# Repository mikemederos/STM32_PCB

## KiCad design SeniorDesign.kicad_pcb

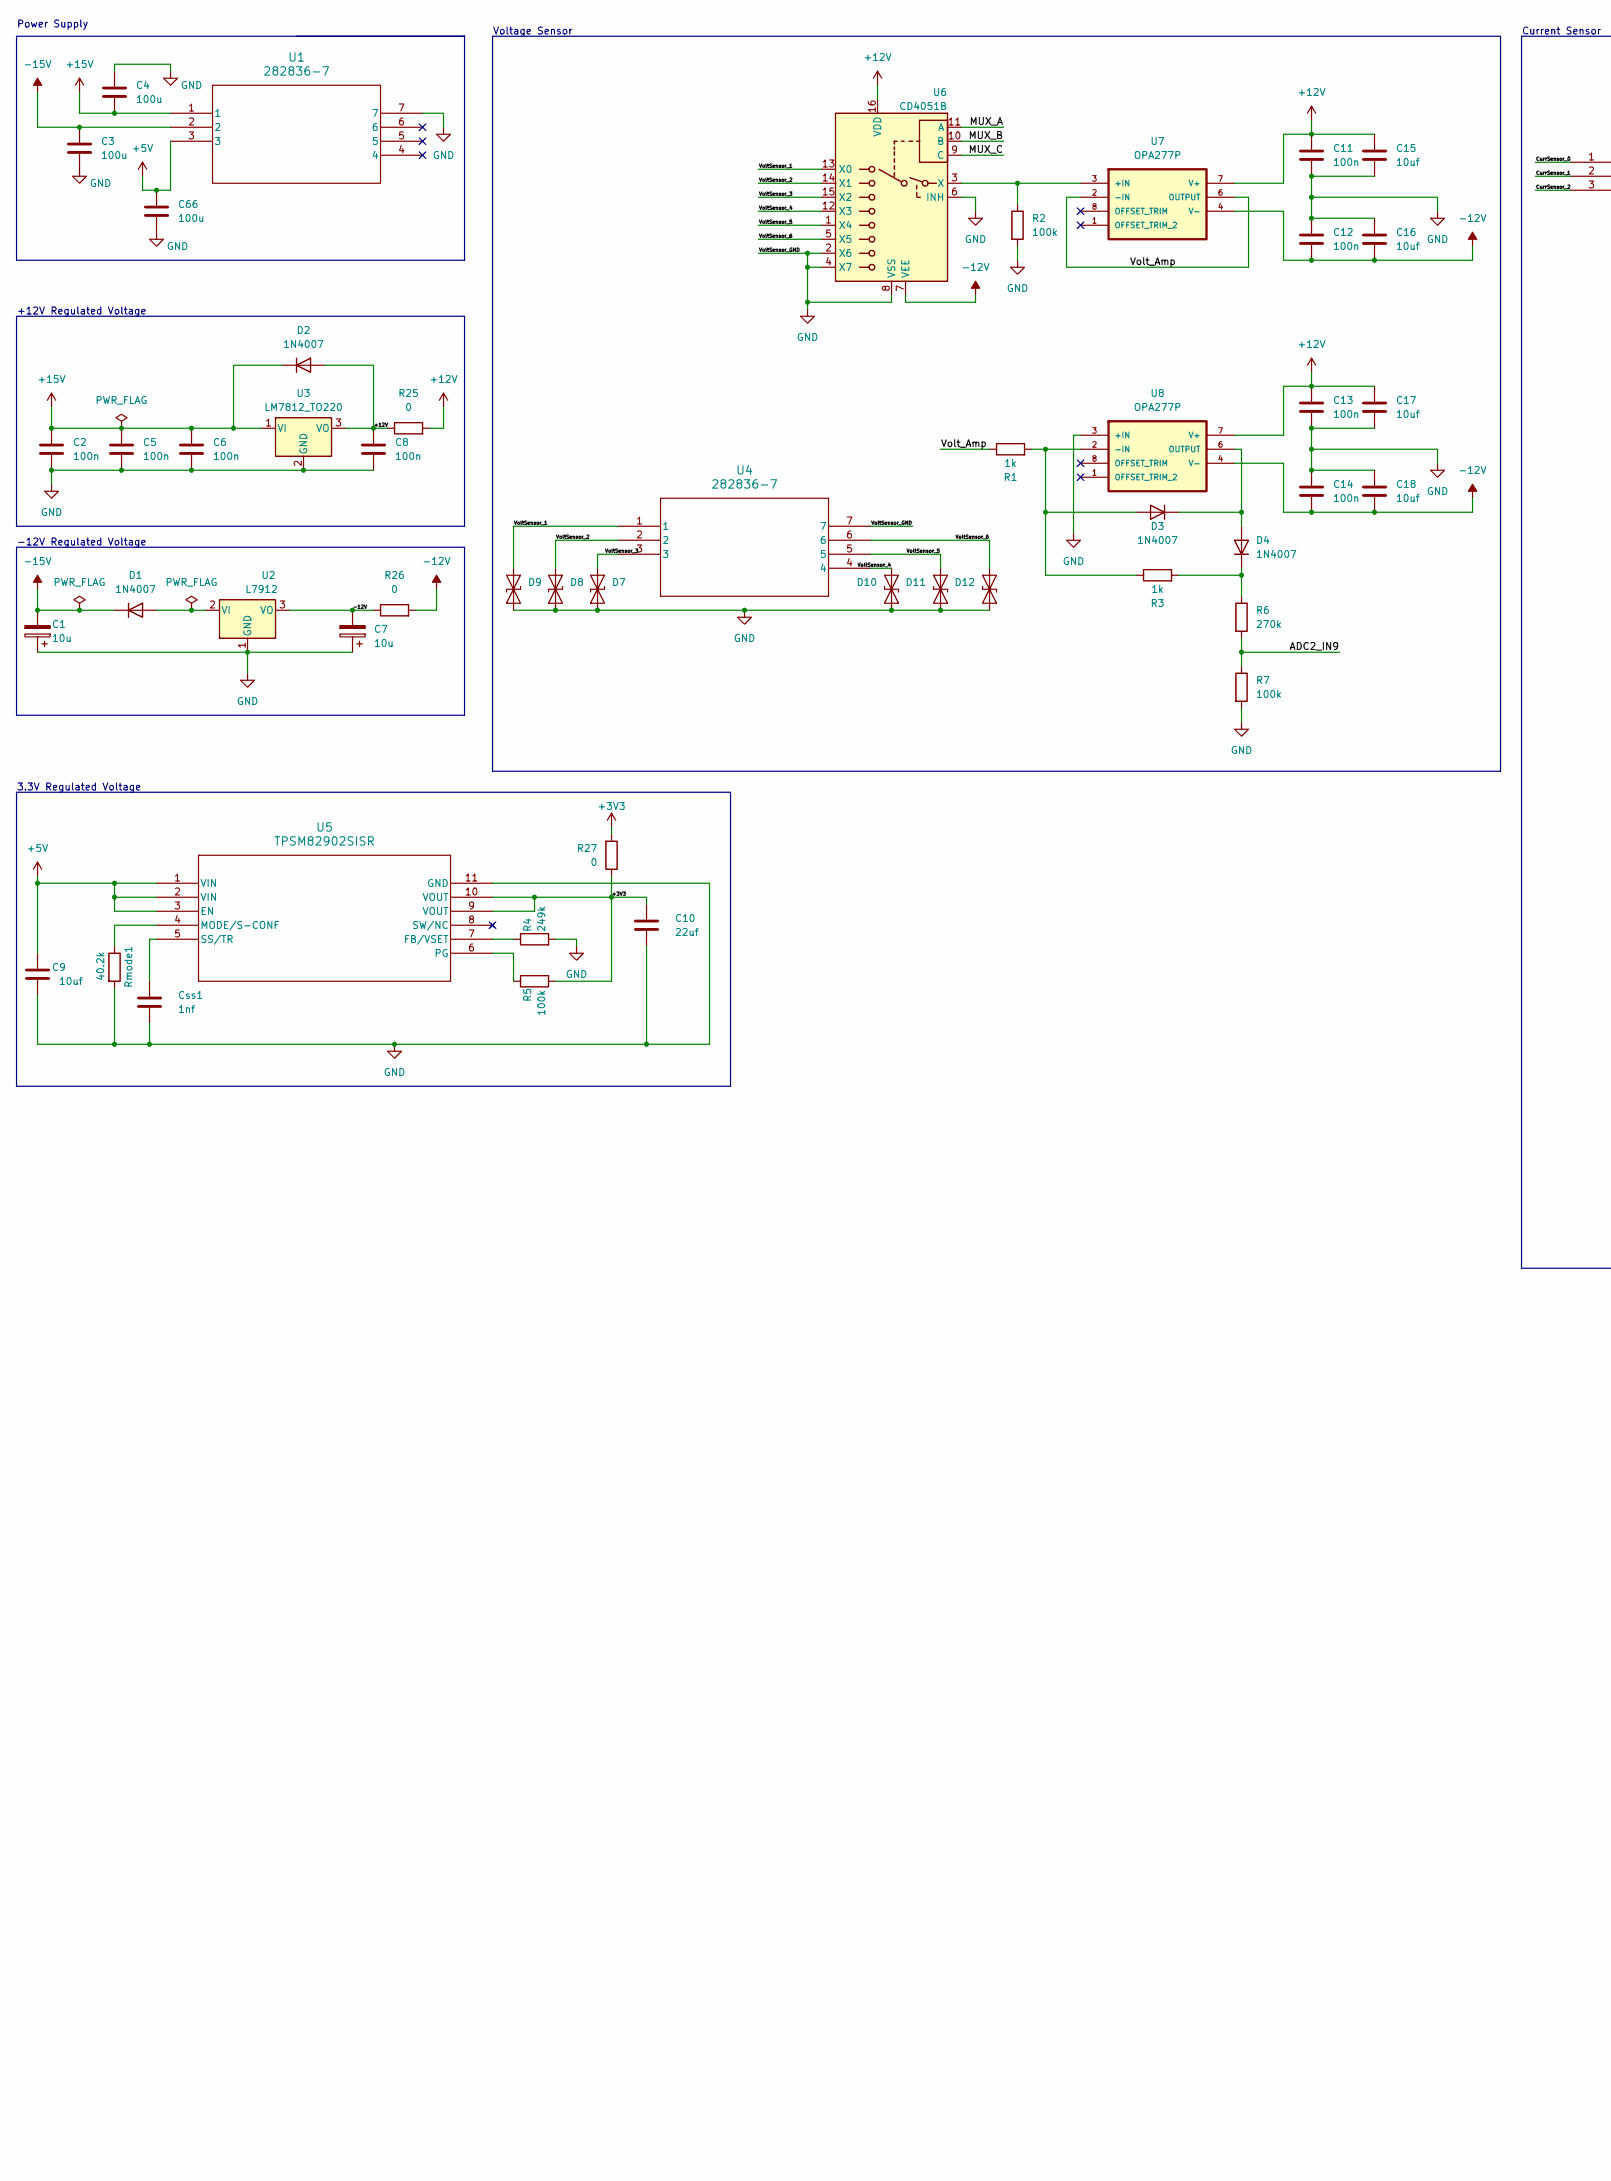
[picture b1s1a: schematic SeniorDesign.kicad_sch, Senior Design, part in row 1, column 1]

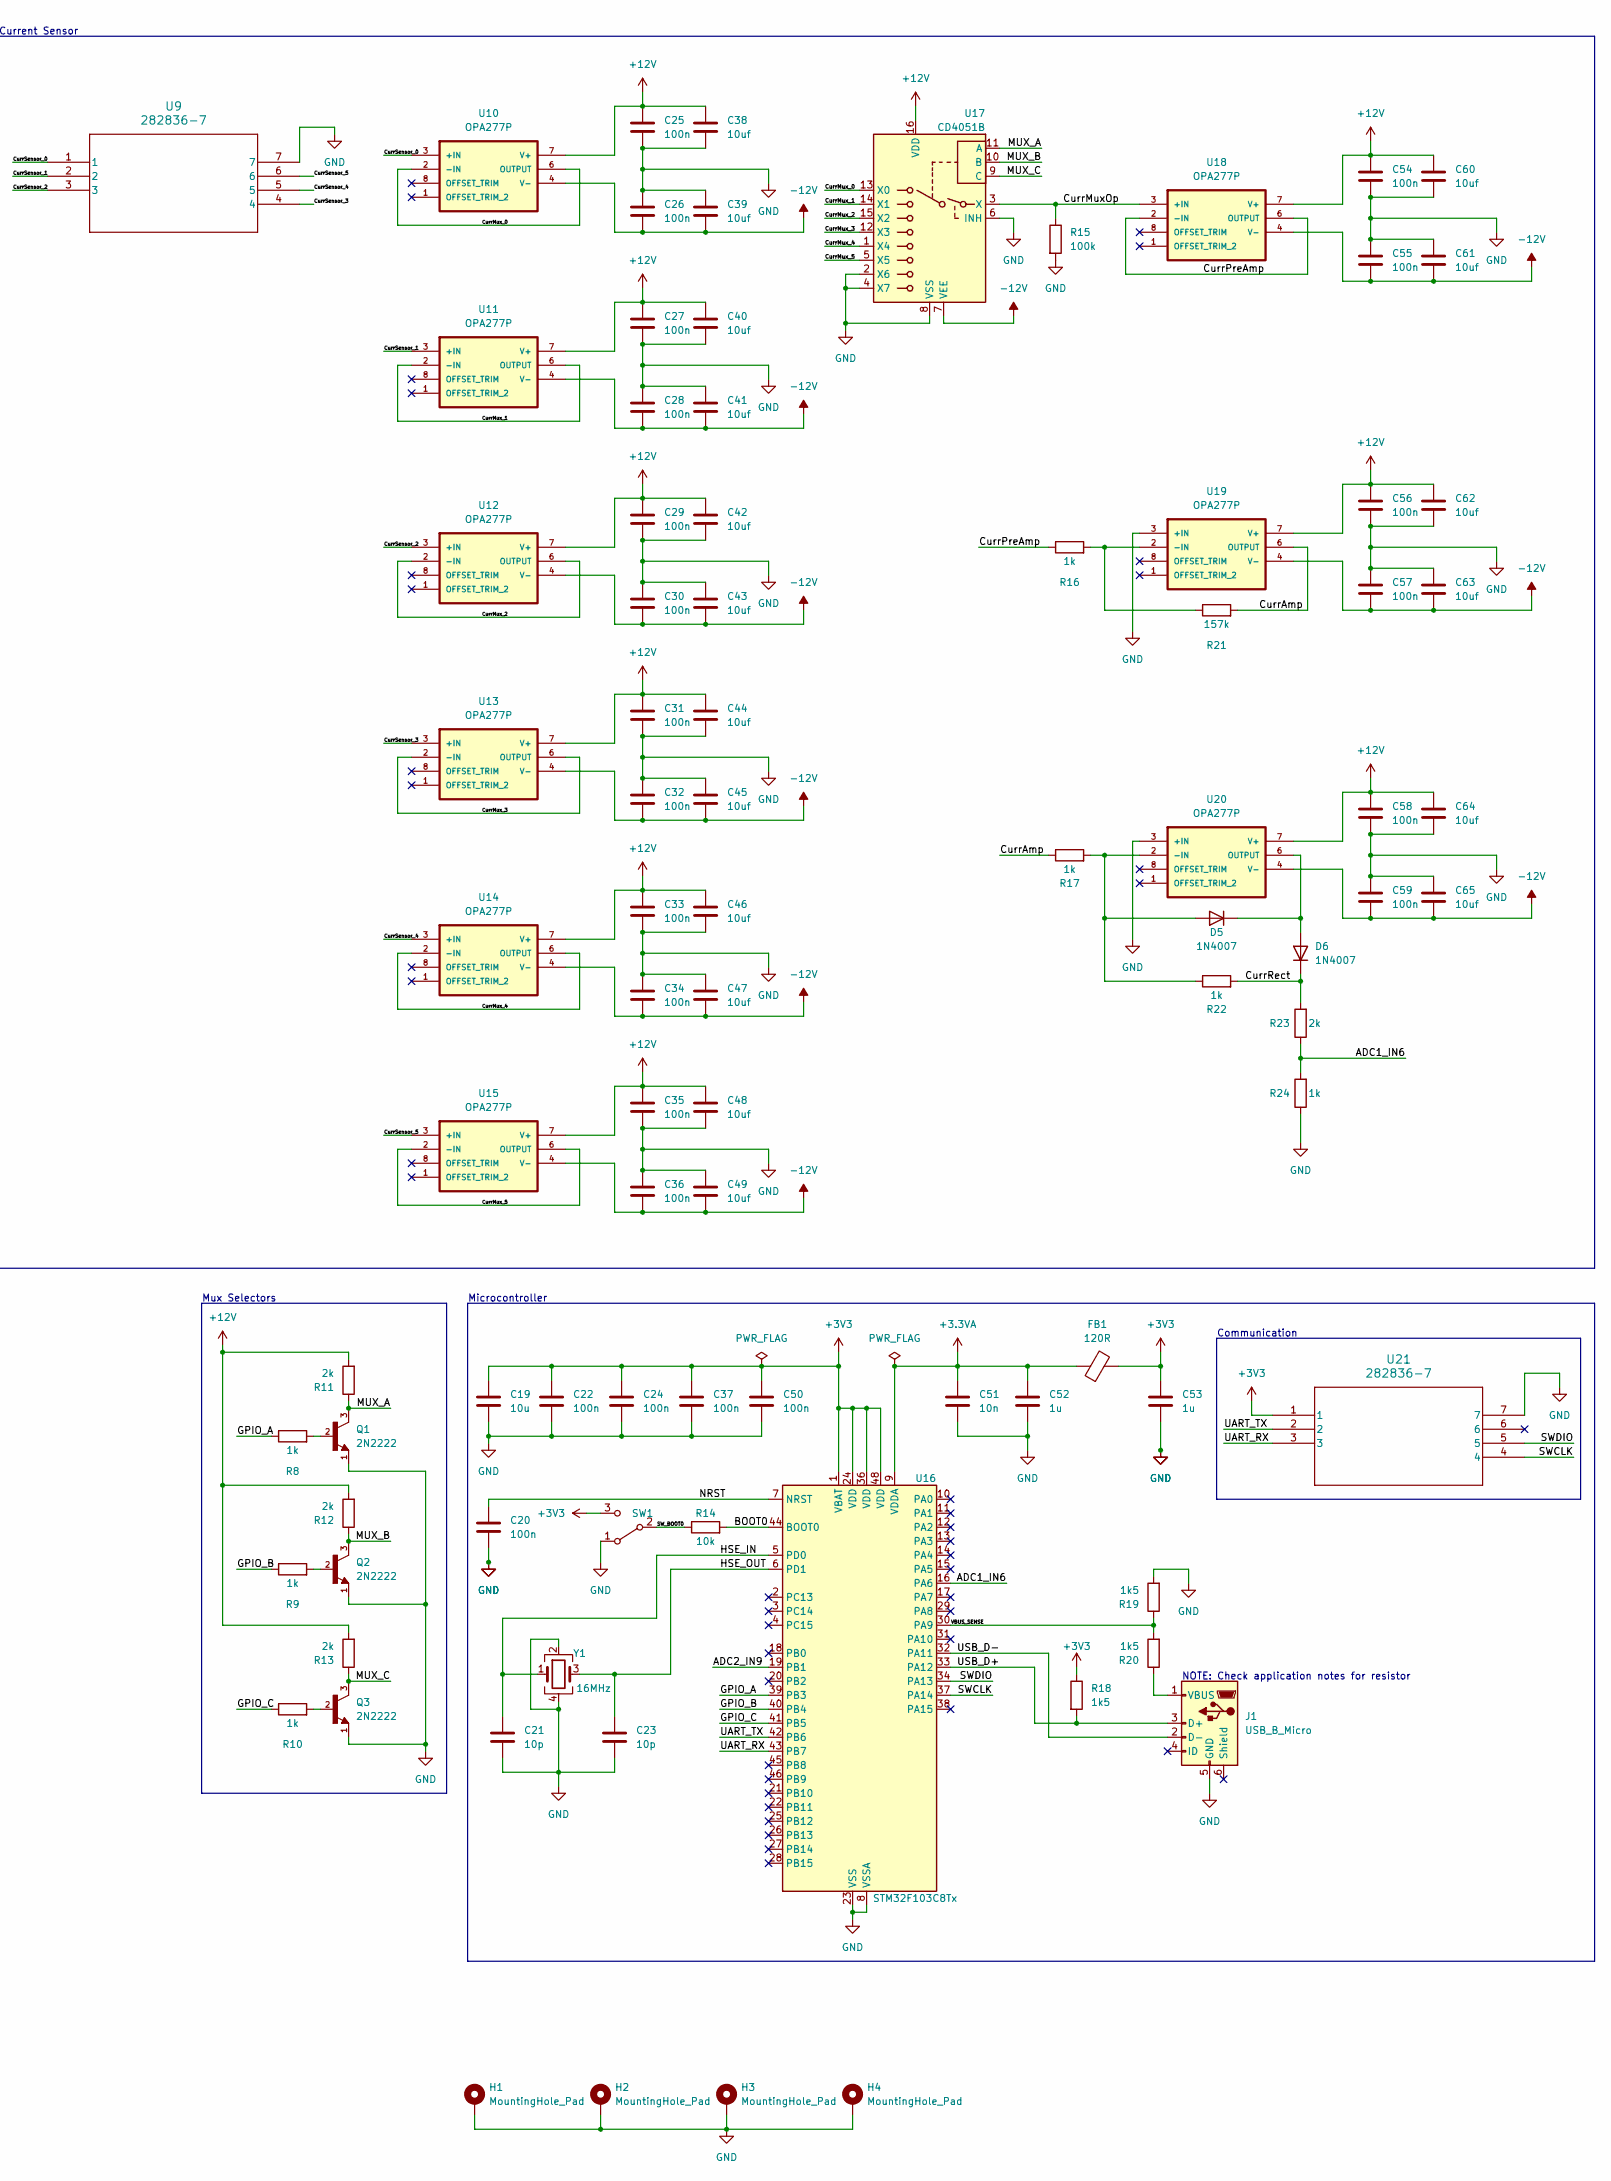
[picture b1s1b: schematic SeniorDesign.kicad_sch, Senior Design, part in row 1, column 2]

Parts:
C1, C7: 10u; CP_Elec_4x5.4
C2, C5, C6, C8, C11, C12, C13, C14, C20, C22, C24, C25, C26, C27, C28, C29, C30, C31, C32, C33, C34, C35, C36, C37, C50, C54, C55, C56, C57, C58, C59: 100n; C_0603_1608Metric
C3, C4, C66: 100u; C_0603_1608Metric
C9, C15, C16, C17, C18, C38, C39, C40, C41, C42, C43, C44, C45, C46, C47, C48, C49, C60, C61, C62, C63, C64, C65: 10uf; C_0603_1608Metric
C10: 22uf; C_0603_1608Metric
C19: 10u; C_0603_1608Metric
C21, C23: 10p; C_0603_1608Metric
C51: 10n; C_0603_1608Metric
C52, C53: 1u; C_0603_1608Metric
Css1: 1nf; C_0603_1608Metric
D1, D2, D3, D4, D5, D6: 1N4007; D_DO-41_SOD81_P10.16mm_Horizontal
D7, D8, D9, D10, D11, D12: SMAJ12CA; D_SMA
FB1: 120R; L_0603_1608Metric
H1, H2, H3, H4: MountingHole_Pad; MountingHole_2.2mm_M2
J1: USB_B_Micro; USB_Micro-B_Wuerth_629105150521
Q1, Q2, Q3: 2N2222; TO127P584H533-3; PARTREV R2
R1, R3, R8, R9, R10, R16, R17, R22, R24: 1k; R_0603_1608Metric
R2, R5, R7, R15: 100k; R_0603_1608Metric
R4: 249k; R_0603_1608Metric
R6: 270k; R_0603_1608Metric
R11, R12, R13, R23: 2k; R_0603_1608Metric
R14: 10k; R_0603_1608Metric
R18, R19, R20: 1k5; R_0603_1608Metric
R21: 157k; R_0603_1608Metric
R25, R26, R27: 0; R_0603_1608Metric
Rmode1: 40.2k; R_0603_1608Metric
SW1: SW_SPDT; SW_SPDT_PCM12
U1, U4, U9, U21: 282836-7; 282836-7_TYC
U2: L7912; TO-220-3_Vertical
U3: LM7812_TO220; TO-220-3_Vertical
U5: TPSM82902SISR; uSIP11_SIS_TEX
U6, U17: CD4051B; D16
U7, U8, U10, U11, U12, U13, U14, U15, U18, U19, U20: OPA277P; DIP794W45P254L959H508Q8
U16: STM32F103C8Tx; LQFP-48_7x7mm_P0.5mm
Y1: 16MHz; Crystal_SMD_3225-4Pin_3.2x2.5mm

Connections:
+3.3VA: C51.1, C52.1, FB1.1, U16.9 (VDDA)
+3V3: C10.1, C19.1, C22.1, C24.1, C37.1, C50.1, C53.1, FB1.2, R5.1, R18.1, R27.1, R27.2, SW1.3 (C), U5.9 (VOUT), U5.10 (VOUT), U16.1 (VBAT), U16.24 (VDD), U16.36 (VDD), U16.48 (VDD), U21.1
+5V: C9.1, C66.1, U1.3, U5.1 (VIN), U5.2 (VIN), U5.3 (EN)
+12V: C8.1, C11.1, C13.1, C15.1, C17.1, C25.1, C27.1, C29.1, C31.1, C33.1, C35.1, C38.1, C40.1, C42.1, C44.1, C46.1, C48.1, C54.1, C56.1, C58.1, C60.1, C62.1, C64.1, D2.2 (A), R11.2, R12.2, R13.2, R25.1, R25.2, U3.3 (VO), U6.16 (VDD), U7.7 (V+), U8.7 (V+), U10.7 (V+), U11.7 (V+), U12.7 (V+), U13.7 (V+), U14.7 (V+), U15.7 (V+), U17.16 (VDD), U18.7 (V+), U19.7 (V+), U20.7 (V+)
+15V: C2.1, C4.2, C5.1, C6.1, D2.1 (K), U1.1, U3.1 (VI)
-12V: C7.2, C12.2, C14.2, C16.2, C18.2, C26.2, C28.2, C30.2, C32.2, C34.2, C36.2, C39.2, C41.2, C43.2, C45.2, C47.2, C49.2, C55.2, C57.2, C59.2, C61.2, C63.2, C65.2, R26.1, R26.2, U2.3 (VO), U6.7 (VEE), U7.4 (V-), U8.4 (V-), U10.4 (V-), U11.4 (V-), U12.4 (V-), U13.4 (V-), U14.4 (V-), U15.4 (V-), U17.7 (VEE), U18.4 (V-), U19.4 (V-), U20.4 (V-)
-15V: C1.2, C3.1, D1.1 (K), U1.2
/ADC1_IN6: R23.1, R24.2, U16.16 (PA6)
/ADC2_IN9: R6.2, R7.1, U16.19 (PB1)
/BOOT0: R14.2, U16.44 (BOOT0)
/CurrAmp: R17.1, R21.2, U19.6 (OUTPUT)
/CurrMuxOp: R15.1, U17.3 (X), U18.3 (+IN)
/CurrMux_0: U10.2 (-IN), U10.6 (OUTPUT), U17.13 (X0)
/CurrMux_1: U11.2 (-IN), U11.6 (OUTPUT), U17.14 (X1)
/CurrMux_2: U12.2 (-IN), U12.6 (OUTPUT), U17.15 (X2)
/CurrMux_3: U13.2 (-IN), U13.6 (OUTPUT), U17.12 (X3)
/CurrMux_4: U14.2 (-IN), U14.6 (OUTPUT), U17.1 (X4)
/CurrMux_5: U15.2 (-IN), U15.6 (OUTPUT), U17.5 (X5)
/CurrPreAmp: R16.1, U18.2 (-IN), U18.6 (OUTPUT)
/CurrRect: D6.1 (K), R22.2, R23.2
/CurrSensor_0: U9.1, U10.3 (+IN)
/CurrSensor_1: U9.2, U11.3 (+IN)
/CurrSensor_2: U9.3, U12.3 (+IN)
/CurrSensor_3: U9.4, U13.3 (+IN)
/CurrSensor_4: U9.5, U14.3 (+IN)
/CurrSensor_5: U9.6, U15.3 (+IN)
/GPIO_A: R8.1, U16.39 (PB3)
/GPIO_B: R9.1, U16.40 (PB4)
/GPIO_C: R10.1, U16.41 (PB5)
/HSE_IN: C21.1, U16.5 (PD0), Y1.1
/HSE_OUT: C23.1, U16.6 (PD1), Y1.3
/MUX_A: Q1.3, R11.1, U6.11 (A), U17.11 (A)
/MUX_B: Q2.3, R12.1, U6.10 (B), U17.10 (B)
/MUX_C: Q3.3, R13.1, U6.9 (C), U17.9 (C)
/NRST: C20.1, U16.7 (NRST)
/SWCLK: U16.37 (PA14), U21.4
/SWDIO: U16.34 (PA13), U21.5
/SW_BOOT0: R14.1, SW1.2 (B)
/UART_RX: U16.43 (PB7), U21.3
/UART_TX: U16.42 (PB6), U21.2
/USB_D+: J1.3 (D+), R18.2, U16.33 (PA12)
/USB_D-: J1.2 (D-), U16.32 (PA11)
/VBUS_SENSE: R19.1, R20.2, U16.30 (PA9)
/VoltSensor_1: D9.2 (A2), U4.1, U6.13 (X0)
/VoltSensor_2: D8.2 (A2), U4.2, U6.14 (X1)
/VoltSensor_3: D7.2 (A2), U4.3, U6.15 (X2)
/VoltSensor_4: D10.2 (A2), U4.4, U6.12 (X3)
/VoltSensor_5: D11.2 (A2), U4.5, U6.1 (X4)
/VoltSensor_6: D12.2 (A2), U4.6, U6.5 (X5)
/Volt_Amp: R1.1, U7.2 (-IN), U7.6 (OUTPUT)
GND: C1.1, C2.2, C3.2, C4.1, C5.2, C6.2, C7.1, C8.2, C9.2, C10.2, C11.2, C12.1, C13.2, C14.1, C15.2, C16.1, C17.2, C18.1, C19.2, C20.2, C21.2, C22.2, C23.2, C24.2, C25.2, C26.1, C27.2, C28.1, C29.2, C30.1, C31.2, C32.1, C33.2, C34.1, C35.2, C36.1, C37.2, C38.2, C39.1, C40.2, C41.1, C42.2, C43.1, C44.2, C45.1, C46.2, C47.1, C48.2, C49.1, C50.2, C51.2, C52.2, C53.2, C54.2, C55.1, C56.2, C57.1, C58.2, C59.1, C60.2, C61.1, C62.2, C63.1, C64.2, C65.1, C66.2, Css1.2, D7.1 (A1), D8.1 (A1), D9.1 (A1), D10.1 (A1), D11.1 (A1), D12.1 (A1), H1.1, H2.1, H3.1, H4.1, J1.5 (GND), Q1.1, Q2.1, Q3.1, R2.2, R4.2, R7.2, R15.2, R19.2, R24.1, Rmode1.2, SW1.1 (A), U1.7, U2.1 (GND), U3.2 (GND), U4.7, U5.11 (GND), U6.2 (X6), U6.4 (X7), U6.6 (INH), U6.8 (VSS), U8.3 (+IN), U9.7, U16.8 (VSSA), U16.23 (VSS), U16.35 (VSS), U16.47 (VSS), U17.2 (X6), U17.4 (X7), U17.6 (INH), U17.8 (VSS), U19.3 (+IN), U20.3 (+IN), U21.7, Y1.2, Y1.4
unnamed: D1.2 (A), U2.2 (VI)
unnamed: D3.2 (A), R1.2, R3.1, U8.2 (-IN)
unnamed: D3.1 (K), D4.2 (A), U8.6 (OUTPUT)
unnamed: D4.1 (K), R3.2, R6.1
unnamed: D5.2 (A), R17.2, R22.1, U20.2 (-IN)
unnamed: D5.1 (K), D6.2 (A), U20.6 (OUTPUT)
unnamed: J1.1 (VBUS), R20.1
unnamed: Q1.2, R8.2
unnamed: Q2.2, R9.2
unnamed: Q3.2, R10.2
unnamed: R4.1, U5.7 (FB/VSET)
unnamed: Rmode1.1, U5.4 (MODE/S-CONF)
unnamed: R5.2, U5.6 (PG)
unnamed: Css1.1, U5.5 (SS/TR)
unnamed: R2.1, U6.3 (X), U7.3 (+IN)
unnamed: R16.2, R21.1, U19.2 (-IN)

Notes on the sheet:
Power Supply
-12V Regulated Voltage
Microcontroller
Mux Selectors
Voltage Sensor
+12V Regulated Voltage
3.3V Regulated Voltage
Communication
Current Sensor
NOTE: Check application notes for resistor

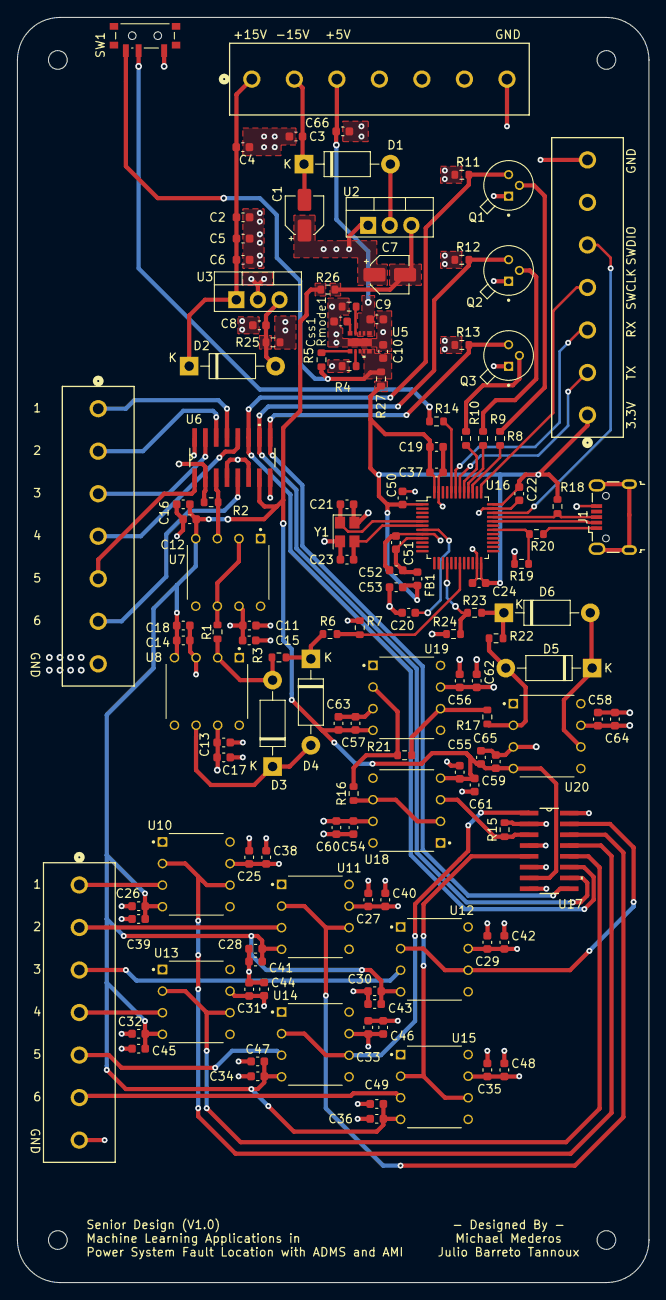
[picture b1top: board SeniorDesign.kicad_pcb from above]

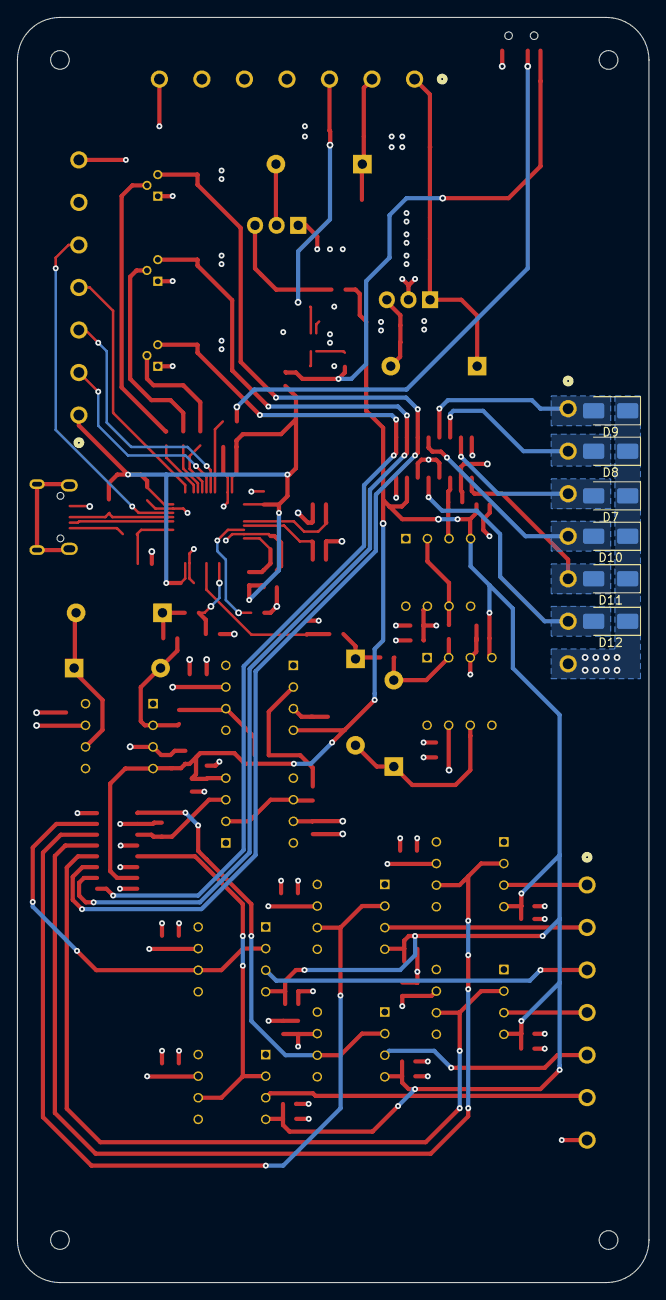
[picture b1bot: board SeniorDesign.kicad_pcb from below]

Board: 4 copper layers, 74.2 x 148.8 mm, 139 parts (6 on the bottom side), 67 nets.

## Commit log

2023-09-21 Add co-author
2023-10-17 10/17/2023
2023-10-18 10/18/2023
2023-10-18 Julio commit 10/18
2023-10-18 Test
2023-10-18 Julio commit 10/18 6:18 PM
2023-10-18 OFuk
2023-10-18 10/18/2023 7:16PM
2023-10-18 10/18/2023 7:22PM
2023-10-24 10/24/2023 2:41PM
2023-10-26 10/26/2023
2023-10-27 10/27/2023
2023-10-30 10/30/2023 12:00AM
2023-11-03 11/3/2023 12:42AM
2023-11-15 11/15/2023 6:50PM
